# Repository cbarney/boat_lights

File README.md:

# boat_lights
Repository to hold important information for boat lights projects

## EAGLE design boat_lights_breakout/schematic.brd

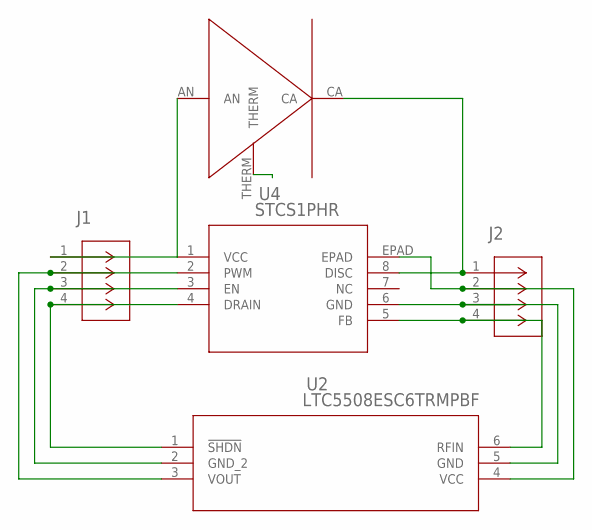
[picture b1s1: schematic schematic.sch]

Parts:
J1, J2: 61300411121; CONN_61300411121_WRE
U2: LTC5508ESC6TRMPBF; SOT-6_SC_LIT
U4: STCS1PHR; POWERSO-8_STM
U$1: MKRAWT-02-0000-0D00J2051

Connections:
unnamed: J1.1, U4.1 (VCC), U$1.AN
unnamed: J1.2, U2.3 (VOUT), U4.2 (PWM)
unnamed: J1.3, U2.2 (GND_2), U4.3 (EN)
unnamed: J1.4, U2.1 (!SHDN), U4.4 (DRAIN)
unnamed: J2.4, U2.6 (RFIN), U4.5 (FB)
unnamed: J2.1, U4.8 (DISC), U$1.CA
unnamed: J2.2, U2.4 (VCC), U4.EPAD
unnamed: J2.3, U2.5 (GND), U4.6 (GND)
THERM: U$1.THERM

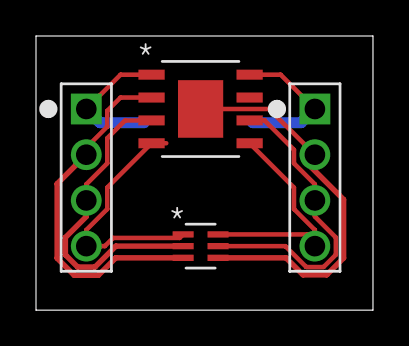
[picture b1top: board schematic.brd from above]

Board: 2 copper layers, 18.7 x 15.2 mm, 5 parts (1 on the bottom side), 8 nets.

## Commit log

2022-05-19 breakout for parts
2022-06-04 Began reciever circuit board
2022-06-08 made progress on reciever board

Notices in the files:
parts and their libraries:
COPYRIGHT: Copyright (C) 2022 Ultra Librarian. All rights reserved.
